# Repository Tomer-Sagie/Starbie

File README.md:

# Starbie
made for hackclub half life event!! following the starbie tutorial, with my own twist on it.

Its basicaly a tamagotchi that you can intertact with through haptics, sound, lights, and a screem as well as a motion sensor which is cool.

## BOM
Check out the bom files for that (Due to the limited funding I get from the starter project, I will only be able to manufacture the base starbie withought my additions. However, I published my full design here to show off my work)

## Important: For the actual files that I will build and put into production, check the sub folders in the hardware, firmware, and gerbers folders named prod____, and the prodBOM

## How it works
I pretty much just followed the given tutorial, but I added two leds, a buzzer for sound, a vibrator for haptics, and a light sensor. It all works through the starbie program that I edited to meet my changes. I am especially proud of the patrick pattern I added to the board ( I worked really hard to keep it there even after all of the changes)

Not much else to say lol, check out my half life project page for the full timeline with timelapses and journal entries n stuff.

## Images

### PCB assembly view

### PCB layout

### Schematic

### Silkscreen pattern detail

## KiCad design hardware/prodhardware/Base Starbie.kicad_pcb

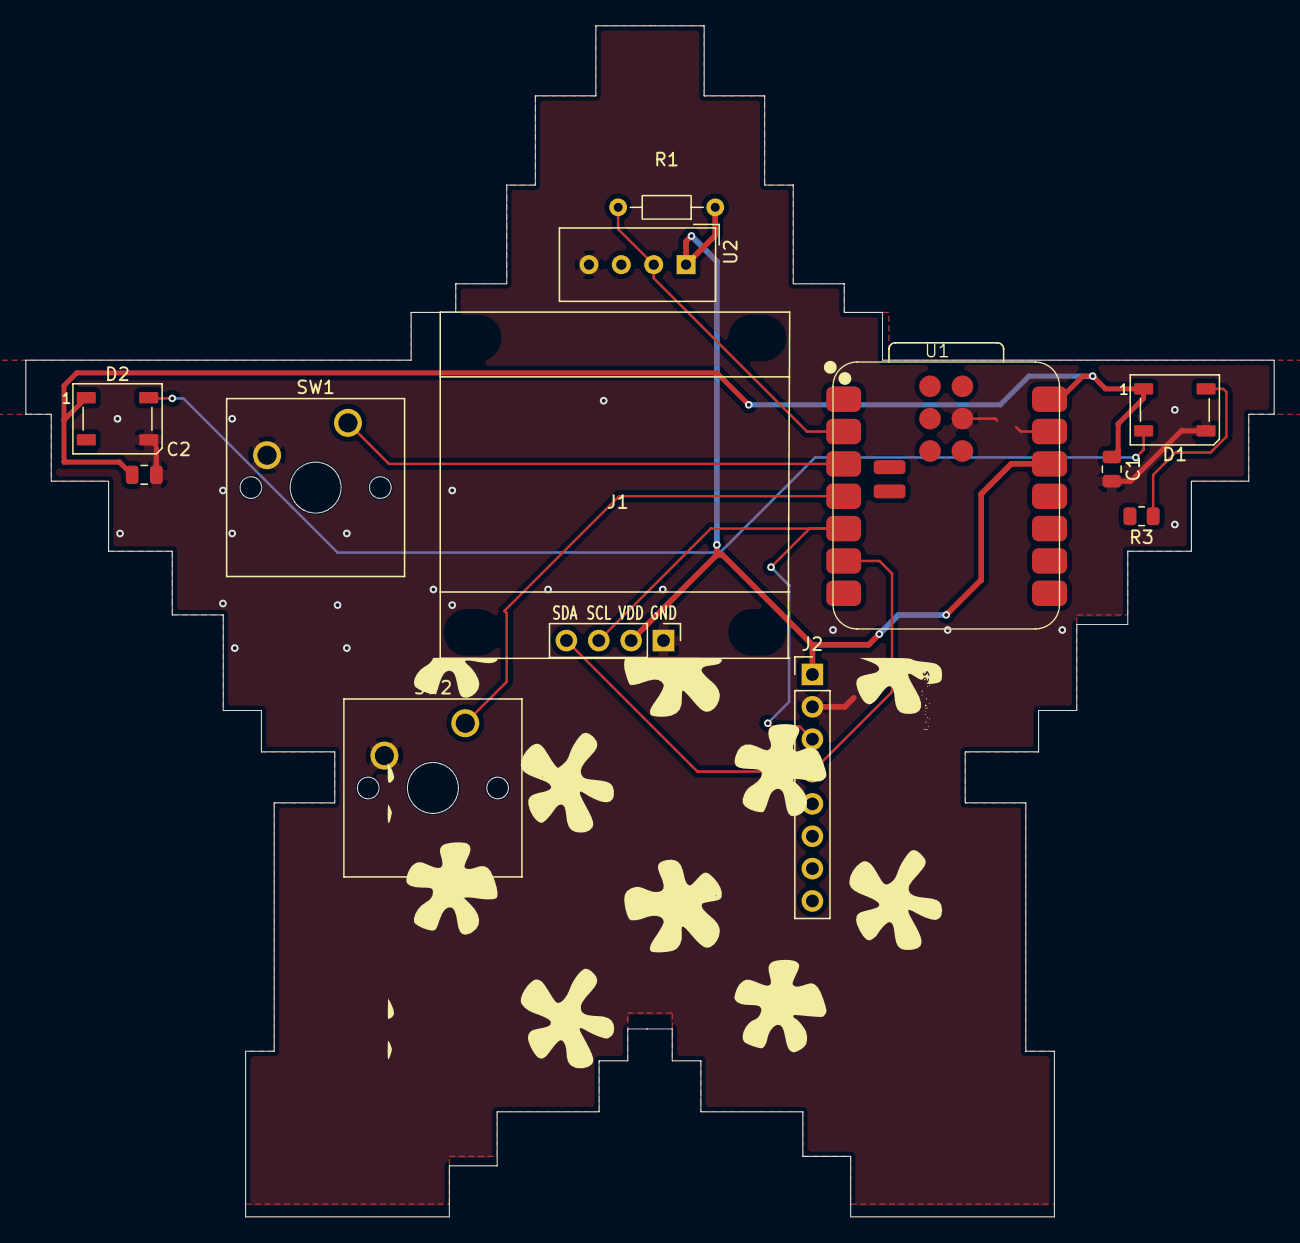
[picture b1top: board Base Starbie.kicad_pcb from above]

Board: 2 copper layers, 98.0 x 93.5 mm, 12 parts (0 on the bottom side), 10 nets.

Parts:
C1, C2: 100nF; C_0805_2012Metric
D1, D2: WS2812B; LED_WS2812B_PLCC4_5.0x5.0mm_P3.2mm
J1: Conn_01x04_Pin; Display_128x64_096_I2C
J2: Conn_01x08_Pin; PinHeader_1x08_P2.54mm_Vertical
R1: 10k; R_Axial_DIN0204_L3.6mm_D1.6mm_P7.62mm_Horizontal
R3: 330Ω; R_0805_2012Metric
SW1, SW2: SW_Push; SW_Cherry_MX_1.00u_PCB
U1: XIAO-ESP32-C3-SMD
U2: DHT11; Aosong_DHT11_5.5x12.0_P2.54mm

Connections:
+3.3V: J1.2, J2.1, R1.1, U1.12 (3V3_OUT), U2.1 (VDD)
+5V: C1.1, C2.1, D1.1 (VDD), D2.1 (VDD), U1.14 (VBUS)
/DHT11 DATA: R1.2, U1.2 (D1), U2.2 (DATA)
/GPIO2: SW1.1, U1.3 (D2)
/GPIO3: SW2.1, U1.4 (D3)
/SCL: J1.3, J2.3, U1.5 (D4)
/SDA: J1.4, J2.4, U1.6 (D5)
GND: C1.2, C2.2, D1.3 (VSS), D2.3 (VSS), J1.1, J2.2, SW1.2, SW2.2, U1.13 (GND), U1.18 (GND), U2.4 (GND)
unnamed: D1.4 (DIN), R3.1
unnamed: D1.2 (DOUT), D2.4 (DIN)
